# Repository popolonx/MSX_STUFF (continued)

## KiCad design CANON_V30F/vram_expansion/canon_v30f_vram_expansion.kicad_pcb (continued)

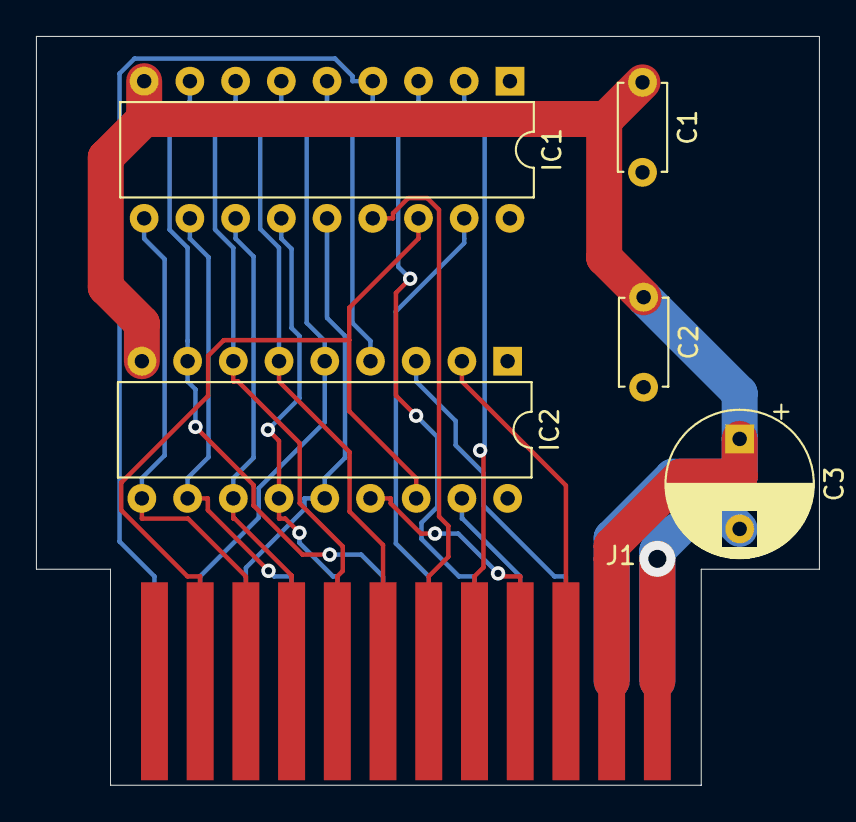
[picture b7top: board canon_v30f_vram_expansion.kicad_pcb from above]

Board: 2 copper layers, 43.5 x 41.6 mm, 6 parts (0 on the bottom side), 21 nets.

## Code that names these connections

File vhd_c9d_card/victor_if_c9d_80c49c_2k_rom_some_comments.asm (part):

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	djnz	r4,L0118    2 x 96h cycles =  300 x 2us = 600us
L011C:   
	jnc	L0120
	anl	p2,#0EFH   BIT4=0 VHD4 set to zero when Carry=1
L0120:
	en	i     #enable external interrupts
	call	L02F2  // start 80us timer
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;
L07D1:  // interrupt occured so here we are
  
 	A= VHD12,VHD10,VHD8, VHD4, x, 0,x,PC0
	cpl	a   // invert from port P2 value
	rlc	a    // rotate left + carry
	    C= _VHD12,  
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L07DC:
	rrc	a  // rotate right + carry
		C= VHD8
		A= VHD12,VHD4, x, 0,x,PC0, old-C, VHD10,
	
	mov	a,r6
	addc	a,#020H
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
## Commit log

2020-11-02 Initial freecad files for nms82xx_front_panel. Design has not been tested at all.
2020-11-02 deleted file as this is now on own sub directory
2020-11-02 Added megaSCSI kicad files.
2020-12-25 hx34 dumped firmware
2020-12-26 Update
    Updated
2021-01-09 update schematics and PCB. added gerber files inside zip.
2021-02-13 Add files via upload
    Video problem
2021-04-27 Add files via upload
    added subschema for analog pcb part
2021-05-08 more analog circuit stuff added.
2021-05-09 added more analog part
2022-06-04 Add files via upload
    corrected reset signals for 8255 and 80C49C
2022-06-04 added real signal names
2022-07-21 added c9c related circuit
    added c9c related circuit for VHD6,7,9 lines, capacitor and resistor values are not known.
2022-07-28 fixed din-8 footprint and scart connections
    din-8 was mirrored, so now corrected. scart pins were not correct related to in and out audio/video. only rca audio/video input was correct towards db25 connector.
2022-07-29 renamed project files and made initial pcb with autorouted tracks
    renamed project files and made initial pcb with autorouted tracks
2022-12-13 Add files via upload
    now reset line is also connected in pcb and some component movement done near crystal.
2023-02-07 corrected CLK signal connection
2023-07-04 Add files via upload
    corrected schematics, rom group pin was invalidly connected to _RAMDIS
2023-07-06 Add files via upload
    corrected audio chip SN76489 data pin connections to datalines to reversed order, so that D0 is connected to SN76489 pin D7, D1 to pin D6, pin D2 to pin D5 and so on.
2023-12-26 Add files via upload
    added tube pcb and front pcb schematics
2023-12-31 added IF box schematics
2024-01-01 initial msx pcb, just components, no wirings
2024-01-02 more MSX pcb schematics
2024-01-02 msx pcb complete, except cassette port related
2024-01-02 shuold be now final
2024-01-03 added filter caps and relay symbol for MSX pcb
2024-01-03 added all variable resistors marked values
2024-01-03 some VRxxx ohm values added
2024-01-03 VR value added
2024-01-04 corrected 4CEE pin mappings to P301 pins and gnd
2024-01-05 corrected vertical drive circuit C310 value
2024-01-05 Changed page size to A1
2024-01-06 corrected wiring for SelectA and SelectB signals
2024-01-06 added some VR usages
2024-09-28 basic file to dump vhd data page addresses
    Basic file to dump vhd data burst starting and stopping page addresses. this will only work if there is no CPU2 as otherwise we get I/O errors to reading page address during VHD data.
2024-09-29 added python script to decode vhd packets from wav
2024-09-29 added -o output file implementation
2025-10-24 electrolytic capacitor list for Victor HD 7500
    Initial electrolytic capacitor list for Victor HD 7500 VHD player
2025-10-24 update some capacitor values and added headers
2025-10-26 removed extra capacitors and regrouped some
2025-10-26 added two capacitors
    added two capacitors under the spindle PCB. Do not know if front panel in player would have also electrolytic capacitors.
2025-10-26 added note about front panel capacitors
2025-10-27 added front panel capacitors
2025-10-27 Update electrolytic capacitor list for Victor HD 7500
2025-11-02 added more VHD player caps
    Added Victor HD 7900 electrolytic caps (some Cxx capacitor ids missing still). Added Sharp VP 2600 player electrolytic caps.
2025-11-02 sorted capacitors
2025-11-03 Update electrolytic capacitor list for Sharp VP-2600
2025-12-06 Add backup recording instructions for game discs
    Instructions for backing up game discs using specific hardware and software.
2025-12-06 adding pictures for instruction file
2025-12-06 Add vdub instructions markdown file
2025-12-06 Convert text instructions to image format
2025-12-06 Update image reference for startup instructions
2025-12-06 Add additional image to vdub instructions
2025-12-06 Add backup instructions for VHD discs
    Provide hardware and software instructions for backing up VHD discs.
2025-12-06 Fix link to vdub instructions and enhance clarity
    Updated link format for vdub instructions and clarified recording process.
2025-12-06 Fix formatting and wording in backup instructions
2025-12-06 Fix typos and enhance backup instructions clarity
    Corrected typos and clarified software download instructions.
2025-12-06 Update backup instructions for clarity and order
2026-01-25 Update electrolytic capacitor list for Victor HD 7900
    corrected some capacitors during recapping the player.
2026-01-25 Update electrolytic capacitor list with additional info
    Added details about original capacitors' temperature rating and pitch.
2026-03-29 Add README for RF capturing from VHD player
2026-03-29 Changed R512 value from 4700M to 0.470R
2026-05-16 Add readme for SVI-105 to MSX adapter
